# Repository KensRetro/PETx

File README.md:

# This project is currently partially complete, please read the following carefully and make an informed decision before you attempt to build it.

I like to provide schematics in Eagle (version 7) because that's what I have used for years at work and it's easy to upgrade the files to 
newer versions or Kicad etc.  It's just a comfort thing for me, but if you change to another format please be sure to carefully check 
that everything looks as it should - conversions don't always go cleanly.  

DISCLAIMER: All information is provided 'AS-IS", I have tried to be as accurate as possible but that doesn't mean there are no mistakes. 
Any errors or omissions etc. are your own responsibility.  

# Project Notes : C64 sized PET - PETx

The prototype is based on the the 9 inch screen version of the PET (board #320349) so no CRTC chip is needed.
I added the video circuit similar to the ones posted around the net
It was also decided to go with a more similar to original re-creation as it makes it easier to substitute parts etc. 
and compatibility remains quite good.

# Changes / Updates in this version (PROTOTYPE): 
1. Added connections for RESET (momentary switch)
2. Added NO_ROM line for diagnostics
3. Added peizo buzzer for standard PET sounds
4. Added Video output circuit - HORIZ/VERT/VIDEO signals no longer attached to USER PORT (I left connection points but will need a
   jumper to connect if needed. This was done in order to facilitate routing, these lines to the user port are normally used for a
   video output circuit, since it's already on-board, it's not likely needed)
5. Added GRAPHIC signal to USER PORT (similar to 12" screen versions)
6. Removed memory expansion connections, definitely won't fit on the board and no known expansion units will fit in the case anyway
7. Changed Video RAM to a single 6116 chip instead of 2 x 2114 (availability)
8. Change ROM set to a single chip, added necessary decoding logic so I/O chip memory is not replaced.
9. Added a jumper to allow multiple ROM sets built in (could be connected to a switch)
10. Changed RAM to a single chip of 32K, this also allowed removal of +12V and -5V supplies and associated components saving a lot of space.
11. Removed CASSETTE #2 as it is rarely used, connection points are still available but no driver for the tape motor was included.
    Connection would have to be wired off the board if needed.
12. Added a couple sets of connection points for +5V and GND for add-ons (normally CASSETTE #1/2 was used for this)
13. Added optional 2nd RAM chip mapped into 9000-FFFF range, jumper (or switch configurable) for only being active over 9000-AFFF or 9000-FFFF for soft ROM option
14. Added option for 2nd RAM (9000-FFFF) to be "READ ONLY" or "READ WRITE"
15. Terminated unused gates to minimize potential noise.
16. Changed ROM socket to allow use of SST39SF010A as well as 27256 (4 ROM sets, Flash ROM, externally programmable)
17. Changed Character ROM to allow more fonts and use of SST39SF010A as well as 27xxx series Eproms.
18. Added power switch & connector that should fit into the existing C64 bracket  (if used)
19. Added access to unused RAM in 8000 area (8400-8FFF)
    
# Potential upgrades not currently incorporated:
(Feel free to suggest others)
1. Add a writable latch that controls some of the dipswitch selectable features above
    
# More Notes:
This project is a PET 2001, 9 inch screen version (started with schematic 320349). This model was chosen for 2 reasons, 
first, a CRTC chip is not required and second, it outputs a near standard video signal with the included interface.
The Intent was to make it fit into a C64 / VIC-20 case.
In order to Achieve this a reduced footprint was needed, so the changes above were implemented.
The parallel and Cassette #1 ports were designed to line up in the same place as the C64/VIC20 version.
The video output appears where the RF output jack was on the C64. This area is in the cartridge slot on the VIC20
The IEEE port appears where the C64 cartridge port was and covers the left 2/3 of the VIC 20 cartridge area.
The placements mean that no/few modifications are needed to the case of the C64 or VIC 20 to fit the board in.
Unfortunately, the power switch and joystick area ends up wide open, with the power switch and power cord coming out in that area.
Perhaps a 3D printed cover could be fashioned as a replacement.
Many other possible upgrades were considered but due to a lack of space and complexity, were rejected (for the prototype run at least).
Perhaps other additions or changes could be incorporated in a future version.
This project depends on the Commodore original prints being correct, some minor corrections were caught, but they were used as a base to start.
The Chip ID's on the silkscreen are those from the original PET layout and start with Uxxx, Chips that start with ICxx are additions or changes 
that have been incorporated to slim the footprint or facilitate routing.
Various keyboard options were considered but again, for the prototype at least, were sticking with a standard C64/VIC20 keyboard and a patched 
version of the edit ROM (or some other available hardware solution)

# BEFORE YOU BUILD:
Some of the parts are near impossible to find, specifically 3446 chips, 74177 chips, and 74154 chips in a DIP package. 
I have a replacement sub-board for the 3446 chips in another repository that has been tested successfully.
You can use 74197 chips as a direct replacement for the 74177, but they are very rare as well.
You can use a newer version of the 74154 chip but it seems to only be available in a SMT version, therefore an adaptor board may need to be created.

# PROTOTYPE VERSION:
This version has been created and tested.  Some small errors were corrected with bodge wires and an added chip and and it seems to function well and passes the diagnostic 
cartridge tests consistantly.

# RELEASE VERSION:
This version HAS NOT been created or tested (I didn't really need another hanging around)
The errors have been corrected in the schematic and board files and Gerbers have been created.

Changes to this version (REV.1) also include the following:
1) Added solder jumpers to allow WD6502 to be used
2) Changed Power supply to 1 regulator
   
TO DO:
1. check/fix alignment of mounting holes to C64 case (Not checked or tested in VIC20 case at this time)

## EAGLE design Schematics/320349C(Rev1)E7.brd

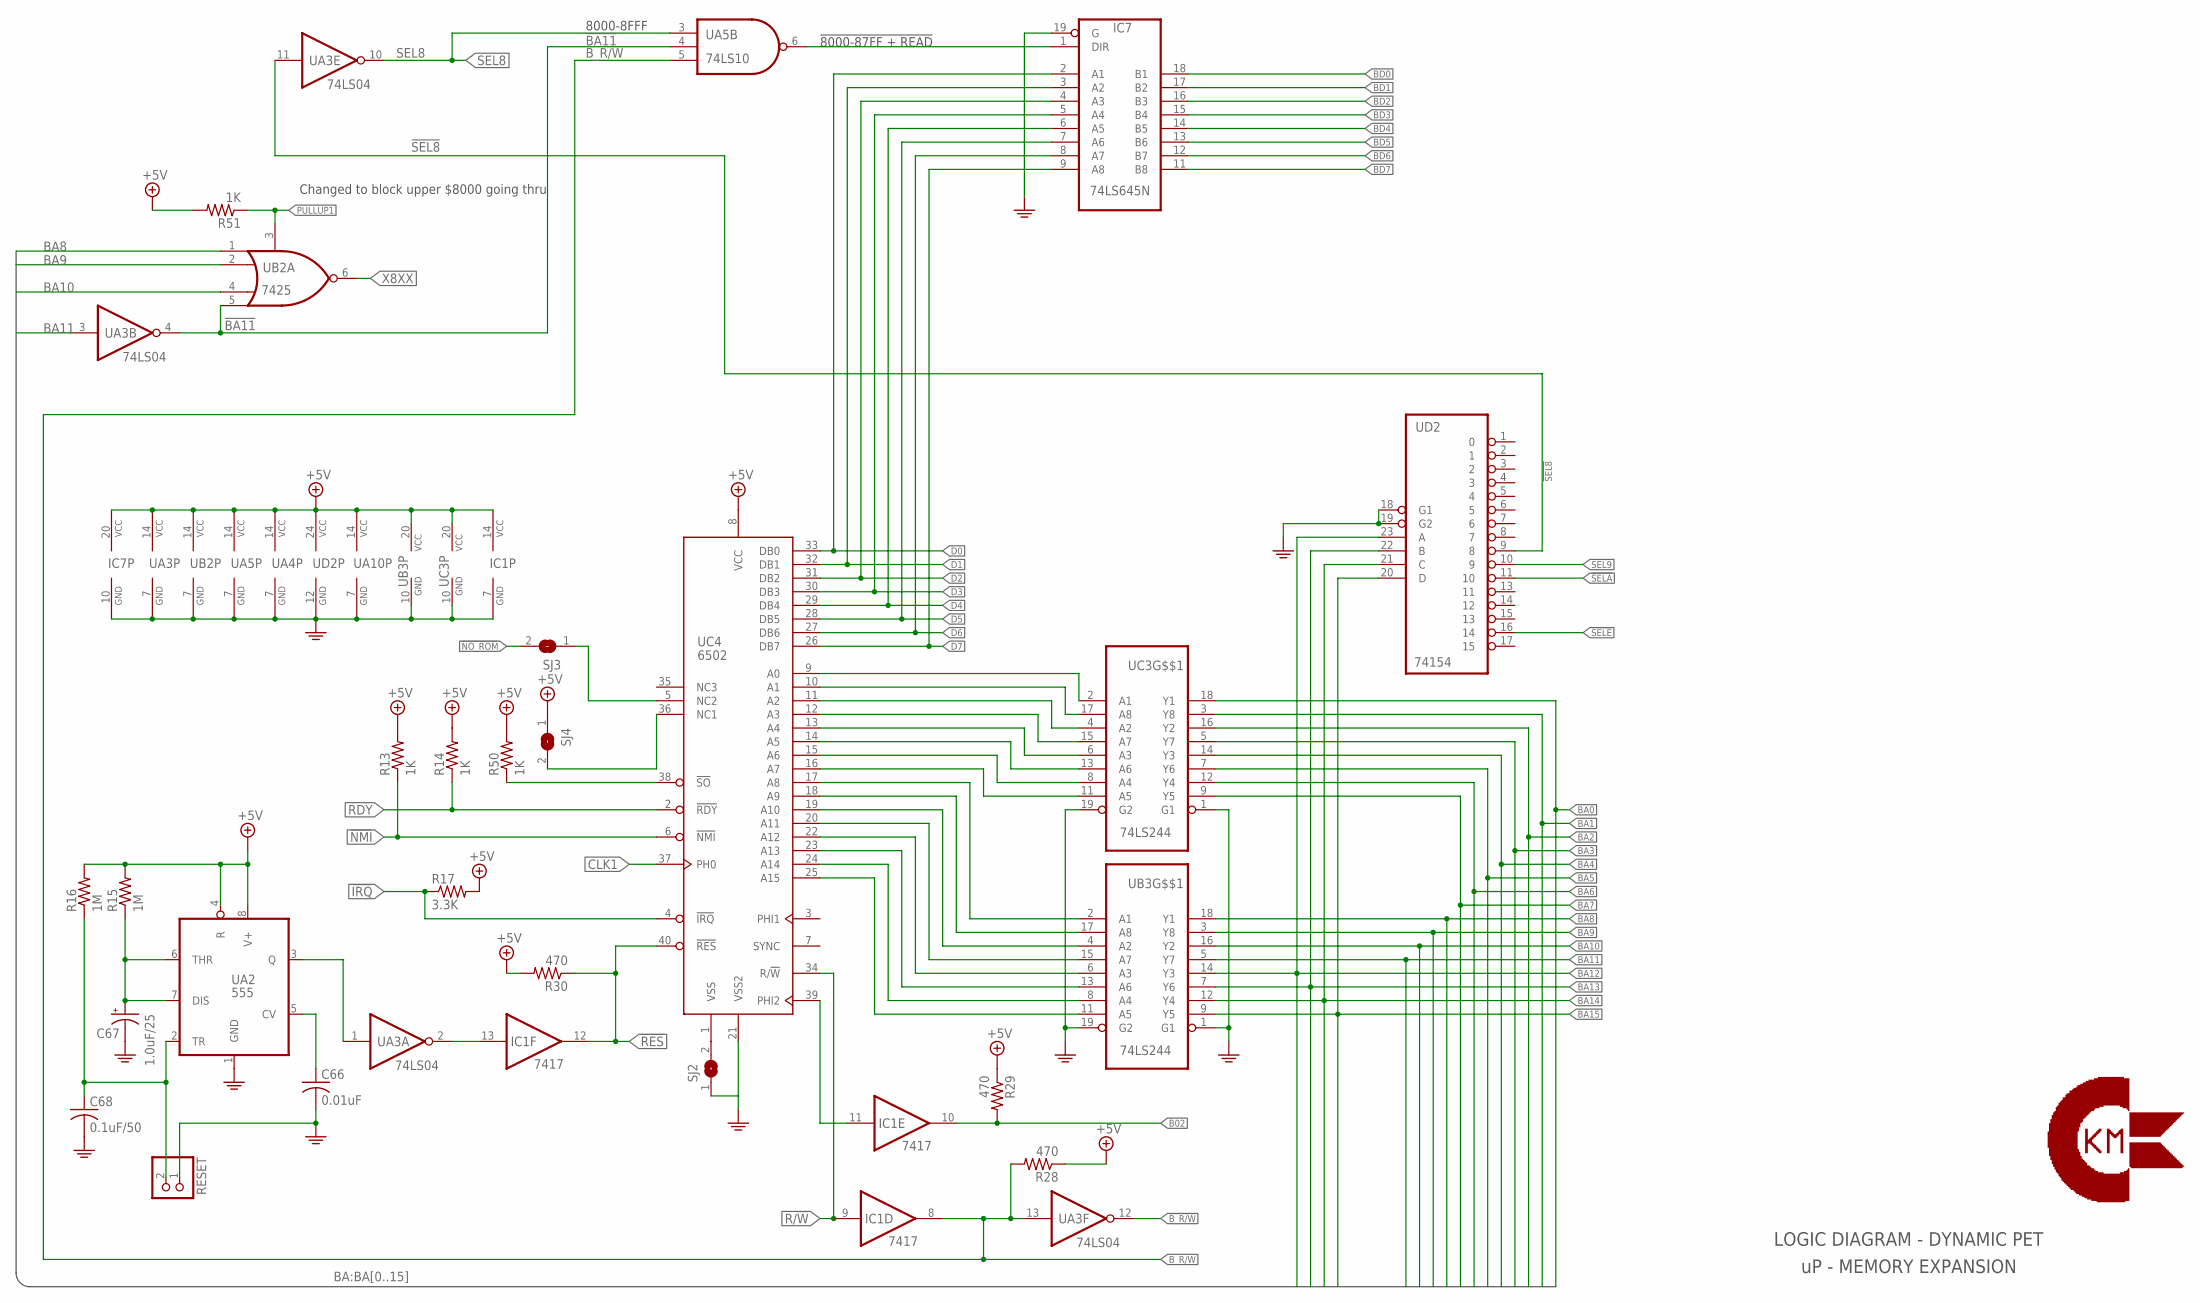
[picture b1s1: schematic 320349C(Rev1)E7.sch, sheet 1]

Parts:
C66: 0.01uF; C025-025X050
C67: 1.0uF/25; E2,5-5
C68: 0.1uF/50; C025-025X050
IC1: 7417; DIL14
IC7: 74LS645N; DIL20
R13, R14, R50, R51: 1K; 0207/10
R15, R16: 1M; 0207/10
R17: 3.3K; 0207/10
R28, R29, R30: 470; 0207/10
RESET: PINHD-1X2; 1X02
SJ2, SJ3, SJ4: SJ
UA2: 555; DIL08
UA3: 74LS04; DIL14
UA4: 74LS00; DIL14
UA5: 74LS10; DIL14
UA10: 7417; DIL14
UB2: 7425; DIL14
UB3: 74LS244; DIL20
UC3: 74LS244; DIL20
UC4: 6502; DIP40
UD2: 74154; DIL24-6

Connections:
!BA11: UA3.4 (O), UA5.4 (I1), UB2.5 (I3); also elsewhere on the board
!B_R/W: UA3.12 (O); also elsewhere on the board
!IRQ: R17.1, UC4.4 (!IRQ); also elsewhere on the board
!NMI: R13.1, UC4.6 (!NMI)
!NO_ROM: SJ3.2; also elsewhere on the board
!RES: IC1.12 (O), R30.1, UC4.40 (!RES); also elsewhere on the board
!SEL8: UA3.11 (I), UD2.9 (8); also elsewhere on the board
!SEL9: UD2.10 (9); also elsewhere on the board
!SELA: UD2.11 (10); also elsewhere on the board
!SELE: UD2.16 (14); also elsewhere on the board
+5V: IC1.14 (VCC), IC7.20 (VCC), R13.2, R14.2, R15.2, R16.2, R17.2, R28.1, R29.1, R30.2, R50.2, R51.2, SJ4.1, UA2.4 (R), UA2.8 (V+), UA3.14 (VCC), UA4.14 (VCC), UA5.14 (VCC), UA10.14 (VCC), UB2.14 (VCC), UB3.20 (VCC), UC3.20 (VCC), UC4.8 (VCC), UD2.24 (VCC); also elsewhere on the board
AB0: UC3.2 (A1), UC4.9 (A0)
AB1: UC3.17 (A8), UC4.10 (A1)
AB2: UC3.4 (A2), UC4.11 (A2)
AB3: UC3.15 (A7), UC4.12 (A3)
AB4: UC3.6 (A3), UC4.13 (A4)
AB5: UC3.13 (A6), UC4.14 (A5)
AB6: UC3.8 (A4), UC4.15 (A6)
AB7: UC3.11 (A5), UC4.16 (A7)
AB8: UB3.2 (A1), UC4.17 (A8)
AB9: UB3.17 (A8), UC4.18 (A9)
AB10: UB3.4 (A2), UC4.19 (A10)
AB11: UB3.15 (A7), UC4.20 (A11)
AB12: UB3.6 (A3), UC4.22 (A12)
AB13: UB3.13 (A6), UC4.23 (A13)
AB14: UB3.8 (A4), UC4.24 (A14)
AB15: UB3.11 (A5), UC4.25 (A15)
B02: IC1.10 (O), R29.2; also elsewhere on the board
BA0: UC3.18 (Y1); also elsewhere on the board
BA1: UC3.3 (Y8); also elsewhere on the board
BA2: UC3.16 (Y2); also elsewhere on the board
BA3: UC3.5 (Y7); also elsewhere on the board
BA4: UC3.14 (Y3); also elsewhere on the board
BA5: UC3.7 (Y6); also elsewhere on the board
BA6: UC3.12 (Y4); also elsewhere on the board
BA7: UC3.9 (Y5); also elsewhere on the board
BA8: UB2.1 (I0), UB3.18 (Y1); also elsewhere on the board
BA9: UB2.2 (I1), UB3.3 (Y8); also elsewhere on the board
BA10: UB2.4 (I2), UB3.16 (Y2); also elsewhere on the board
BA11: UA3.3 (I), UB3.5 (Y7); also elsewhere on the board
BA12: UB3.14 (Y3), UD2.23 (A); also elsewhere on the board
BA13: UB3.7 (Y6), UD2.22 (B); also elsewhere on the board
BA14: UB3.12 (Y4), UD2.21 (C); also elsewhere on the board
BA15: UB3.9 (Y5), UD2.20 (D); also elsewhere on the board
BD0: IC7.18 (B1); also elsewhere on the board
BD1: IC7.17 (B2); also elsewhere on the board
BD2: IC7.16 (B3); also elsewhere on the board
BD3: IC7.15 (B4); also elsewhere on the board
BD4: IC7.14 (B5); also elsewhere on the board
BD5: IC7.13 (B6); also elsewhere on the board
BD6: IC7.12 (B7); also elsewhere on the board
BD7: IC7.11 (B8); also elsewhere on the board
B_R/W: IC1.8 (O), R28.2, UA3.13 (I), UA5.5 (I2); also elsewhere on the board
CLK1: UC4.37 (PH0); also elsewhere on the board
CLK2: IC1.11 (I), UC4.39 (PHI2)
D0: IC7.2 (A1), UC4.33 (DB0); also elsewhere on the board
D1: IC7.3 (A2), UC4.32 (DB1); also elsewhere on the board
D2: IC7.4 (A3), UC4.31 (DB2); also elsewhere on the board
D3: IC7.5 (A4), UC4.30 (DB3); also elsewhere on the board
D4: IC7.6 (A5), UC4.29 (DB4); also elsewhere on the board
D5: IC7.7 (A6), UC4.28 (DB5); also elsewhere on the board
D6: IC7.8 (A7), UC4.27 (DB6); also elsewhere on the board
D7: IC7.9 (A8), UC4.26 (DB7); also elsewhere on the board
GND: C66.2, C67.-, C68.2, IC1.7 (GND), IC7.10 (GND), IC7.19 (G), RESET.1, SJ2.1, UA2.1 (GND), UA3.7 (GND), UA4.7 (GND), UA5.7 (GND), UA10.7 (GND), UB2.7 (GND), UB3.1 (G1), UB3.10 (GND), UB3.19 (G2), UC3.1 (G1), UC3.10 (GND), UC3.19 (G2), UC4.21 (VSS2), UD2.12 (GND), UD2.18 (G1), UD2.19 (G2); also elsewhere on the board
unnamed: IC7.1 (DIR), UA5.6 (O)
unnamed: R50.1, UC4.38 (!SO)
unnamed: C66.1, UA2.5 (CV)
unnamed: C67.+, R15.1, UA2.6 (THR), UA2.7 (DIS)
unnamed: C68.1, R16.1, RESET.2, UA2.2 (TR)
unnamed: IC1.13 (I), UA3.2 (O)
unnamed: UA2.3 (Q), UA3.1 (I)
unnamed: SJ3.1, UC4.5 (NC2)
unnamed: SJ4.2, UC4.36 (NC1)
unnamed: SJ2.2, UC4.1 (VSS)
PULLUP1: R51.1, UB2.3 (G); also elsewhere on the board
R/!W: IC1.9 (I), UC4.34 (R/!W); also elsewhere on the board
RDY: R14.1, UC4.2 (!RDY)
SEL8: UA3.10 (O), UA5.3 (I0); also elsewhere on the board
X8XX: UB2.6 (O); also elsewhere on the board

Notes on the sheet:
LOGIC DIAGRAM - DYNAMIC PET
uP - MEMORY EXPANSION
8000-8FFF
!8000-87FF + READ
Changed to block upper $8000 going thru

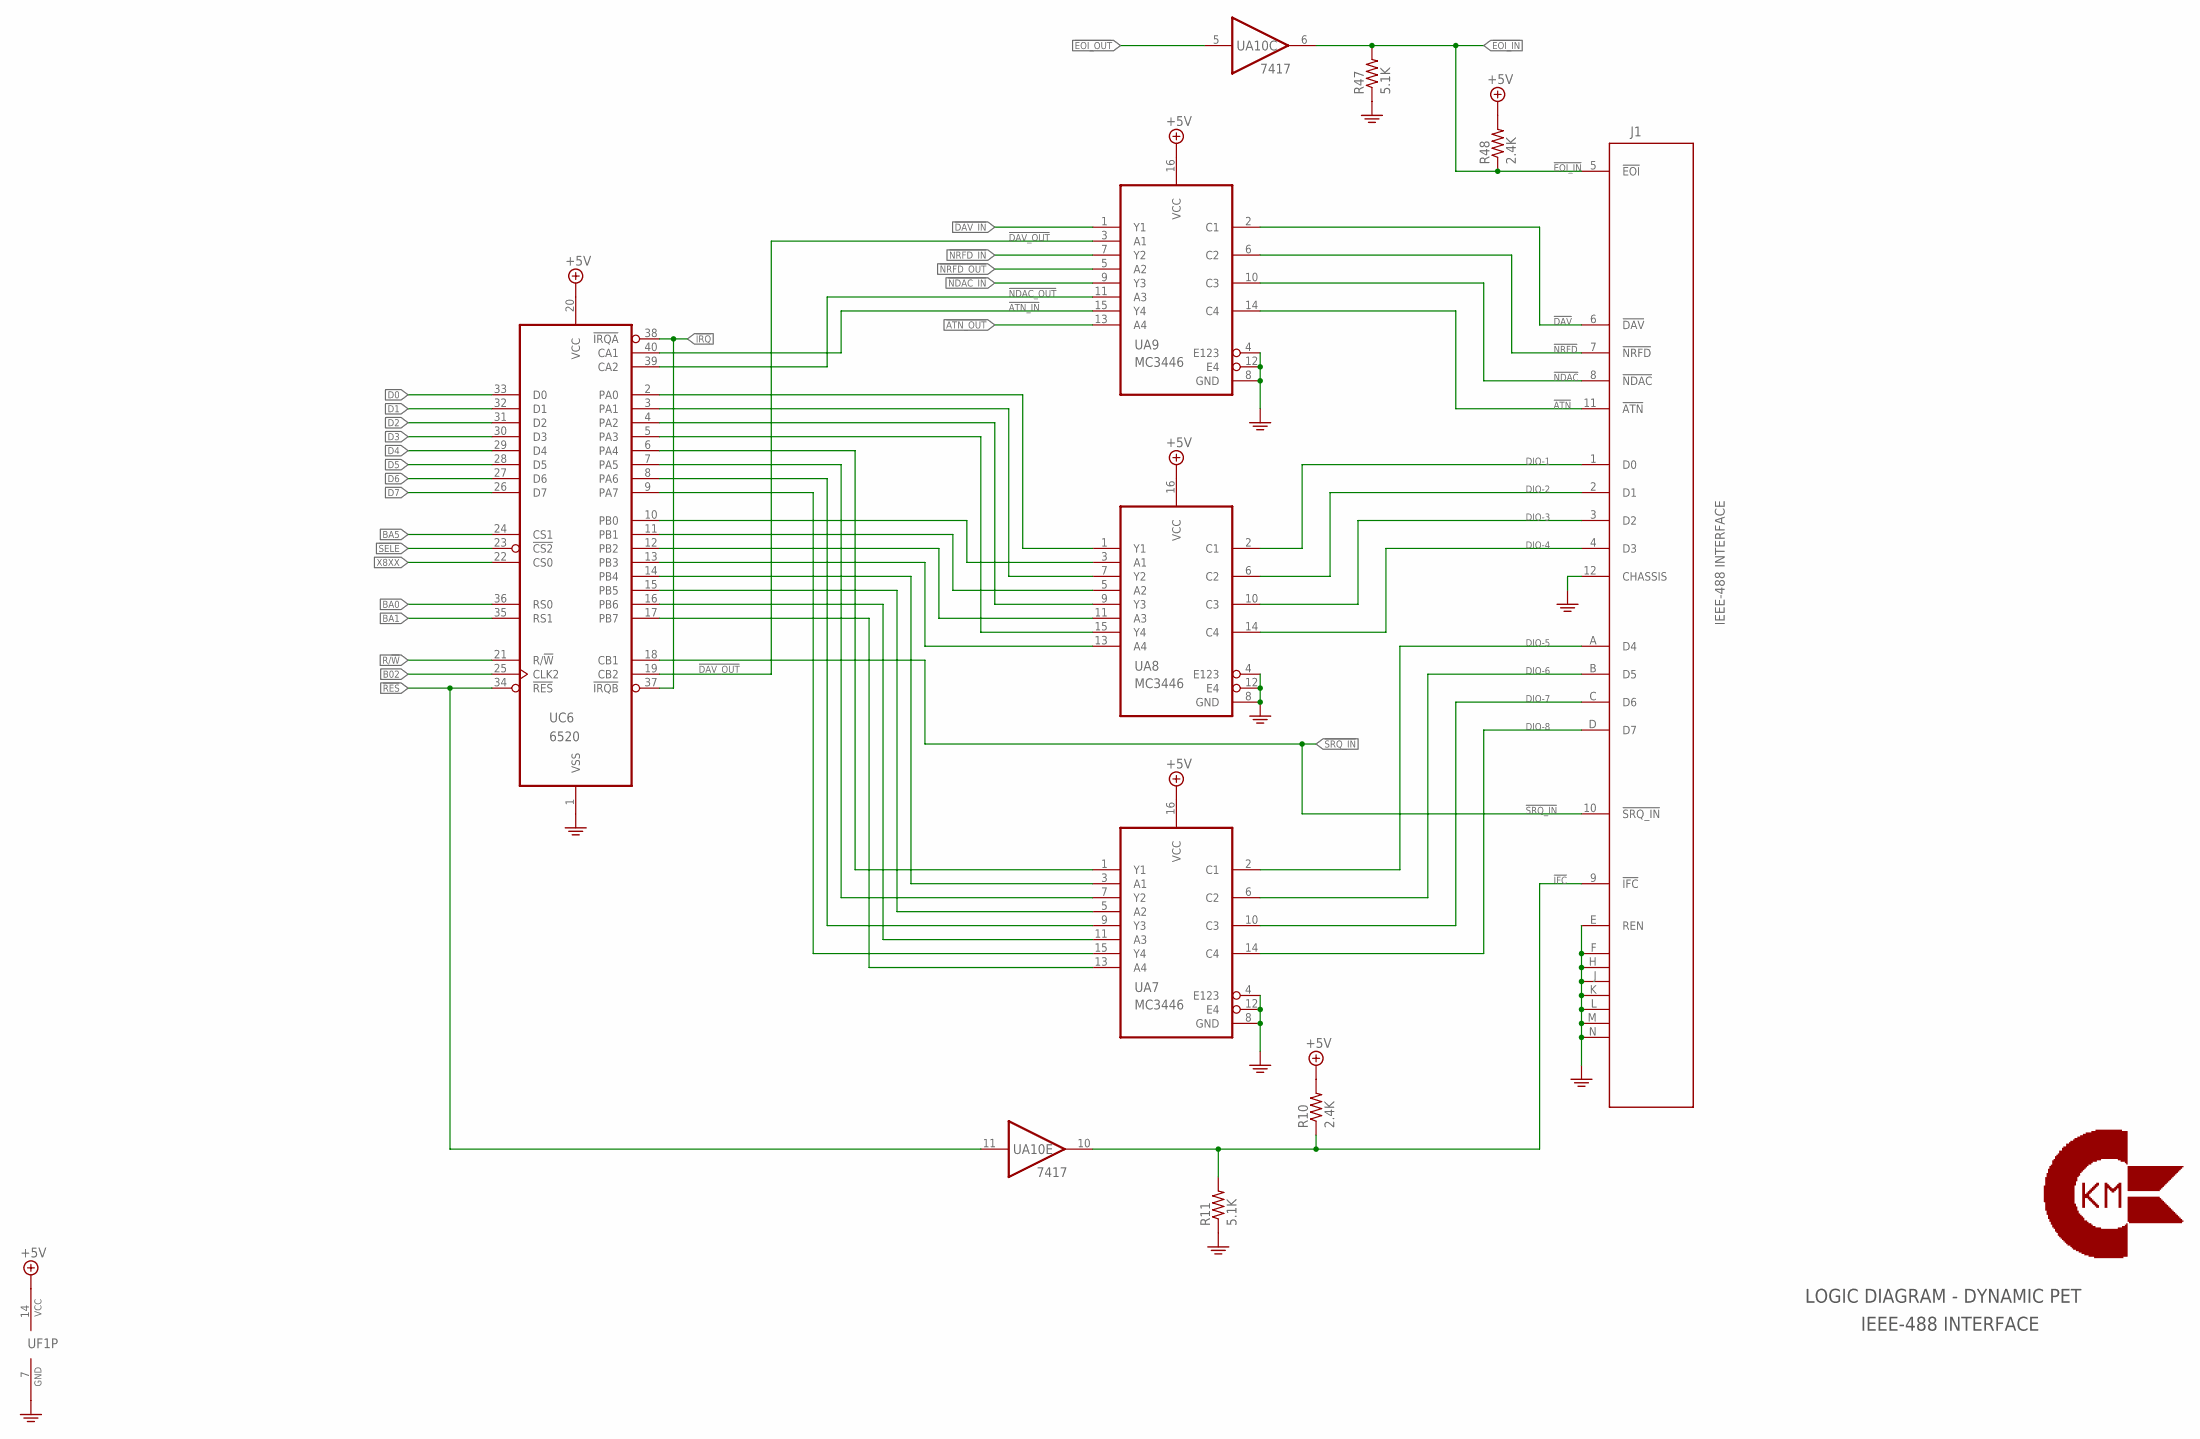
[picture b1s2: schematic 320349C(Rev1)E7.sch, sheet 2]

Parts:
J1: IEEE-488 INTERFACE; UPS24EDGE
R10, R48: 2.4K; 0207/10
R11, R47: 5.1K; 0207/10
U$32: CBM-XL
UA7, UA8, UA9: MC3446; DIL16
UA10: 7417; DIL14
UC6: 6520; DIL40
UF1: 74LS08; DIL14

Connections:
!ATN: J1.11 (!ATN), UA9.14 (C4)
!ATN_IN: UA9.15 (Y4), UC6.40 (CA1)
!ATN_OUT: UA9.13 (A4); also elsewhere on the board
!DAV: J1.6 (!DAV), UA9.2 (C1)
!DAV_IN: UA9.1 (Y1); also elsewhere on the board
!DAV_OUT: UA9.3 (A1), UC6.19 (CB2)
!EOI_IN: J1.5 (!EOI), R47.2, R48.1, UA10.6 (O); also elsewhere on the board
!EOI_OUT: UA10.5 (I); also elsewhere on the board
!IFC: J1.9 (!IFC), R10.1, R11.2, UA10.10 (O)
!IRQ: UC6.37 (!IRQB), UC6.38 (!IRQA); also elsewhere on the board
!NDAC: J1.8 (!NDAC), UA9.10 (C3)
!NDAC_IN: UA9.9 (Y3); also elsewhere on the board
!NDAC_OUT: UA9.11 (A3), UC6.39 (CA2)
!NRFD: J1.7 (!NRFD), UA9.6 (C2)
!NRFD_IN: UA9.7 (Y2); also elsewhere on the board
!NRFD_OUT: UA9.5 (A2); also elsewhere on the board
!RES: UA10.11 (I), UC6.34 (!RES); also elsewhere on the board
!SELE: UC6.23 (!CS2); also elsewhere on the board
!SRQ_IN: J1.10 (!SRQ_IN), UC6.18 (CB1); also elsewhere on the board
+5V: R10.2, R48.2, UA7.16 (VCC), UA8.16 (VCC), UA9.16 (VCC), UC6.20 (VCC), UF1.14 (VCC); also elsewhere on the board
B02: UC6.25 (CLK2); also elsewhere on the board
BA0: UC6.36 (RS0); also elsewhere on the board
BA1: UC6.35 (RS1); also elsewhere on the board
BA5: UC6.24 (CS1); also elsewhere on the board
D0: UC6.33 (D0); also elsewhere on the board
D1: UC6.32 (D1); also elsewhere on the board
D2: UC6.31 (D2); also elsewhere on the board
D3: UC6.30 (D3); also elsewhere on the board
D4: UC6.29 (D4); also elsewhere on the board
D5: UC6.28 (D5); also elsewhere on the board
D6: UC6.27 (D6); also elsewhere on the board
D7: UC6.26 (D7); also elsewhere on the board
DI-1: UA8.1 (Y1), UC6.2 (PA0)
DI-2: UA8.7 (Y2), UC6.3 (PA1)
DI-3: UA8.9 (Y3), UC6.4 (PA2)
DI-4: UA8.15 (Y4), UC6.5 (PA3)
DI-5: UA7.1 (Y1), UC6.6 (PA4)
DI-6: UA7.7 (Y2), UC6.7 (PA5)
DI-7: UA7.9 (Y3), UC6.8 (PA6)
DI-8: UA7.15 (Y4), UC6.9 (PA7)
DIO-1: J1.1 (D0), UA8.2 (C1)
DIO-2: J1.2 (D1), UA8.6 (C2)
DIO-3: J1.3 (D2), UA8.10 (C3)
DIO-4: J1.4 (D3), UA8.14 (C4)
DIO-5: J1.A (D4), UA7.2 (C1)
DIO-6: J1.B (D5), UA7.6 (C2)
DIO-7: J1.C (D6), UA7.10 (C3)
DIO-8: J1.D (D7), UA7.14 (C4)
DO-1: UA8.3 (A1), UC6.10 (PB0)
DO-2: UA8.5 (A2), UC6.11 (PB1)
DO-3: UA8.11 (A3), UC6.12 (PB2)
DO-4: UA8.13 (A4), UC6.13 (PB3)
DO-5: UA7.3 (A1), UC6.14 (PB4)
DO-6: UA7.5 (A2), UC6.15 (PB5)
DO-7: UA7.11 (A3), UC6.16 (PB6)
DO-8: UA7.13 (A4), UC6.17 (PB7)
GND: J1.12 (CHASSIS), J1.E (REN), J1.F (18), J1.H (19), J1.J (20), J1.K (21), J1.L (22), J1.M (23), J1.N (24), R11.1, R47.1, UA7.4 (E123), UA7.8 (GND), UA7.12 (E4), UA8.4 (E123), UA8.8 (GND), UA8.12 (E4), UA9.4 (E123), UA9.8 (GND), UA9.12 (E4), UC6.1 (VSS), UF1.7 (GND); also elsewhere on the board
R/!W: UC6.21 (R/!W); also elsewhere on the board
X8XX: UC6.22 (CS0); also elsewhere on the board

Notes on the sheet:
LOGIC DIAGRAM - DYNAMIC PET
IEEE-488 INTERFACE

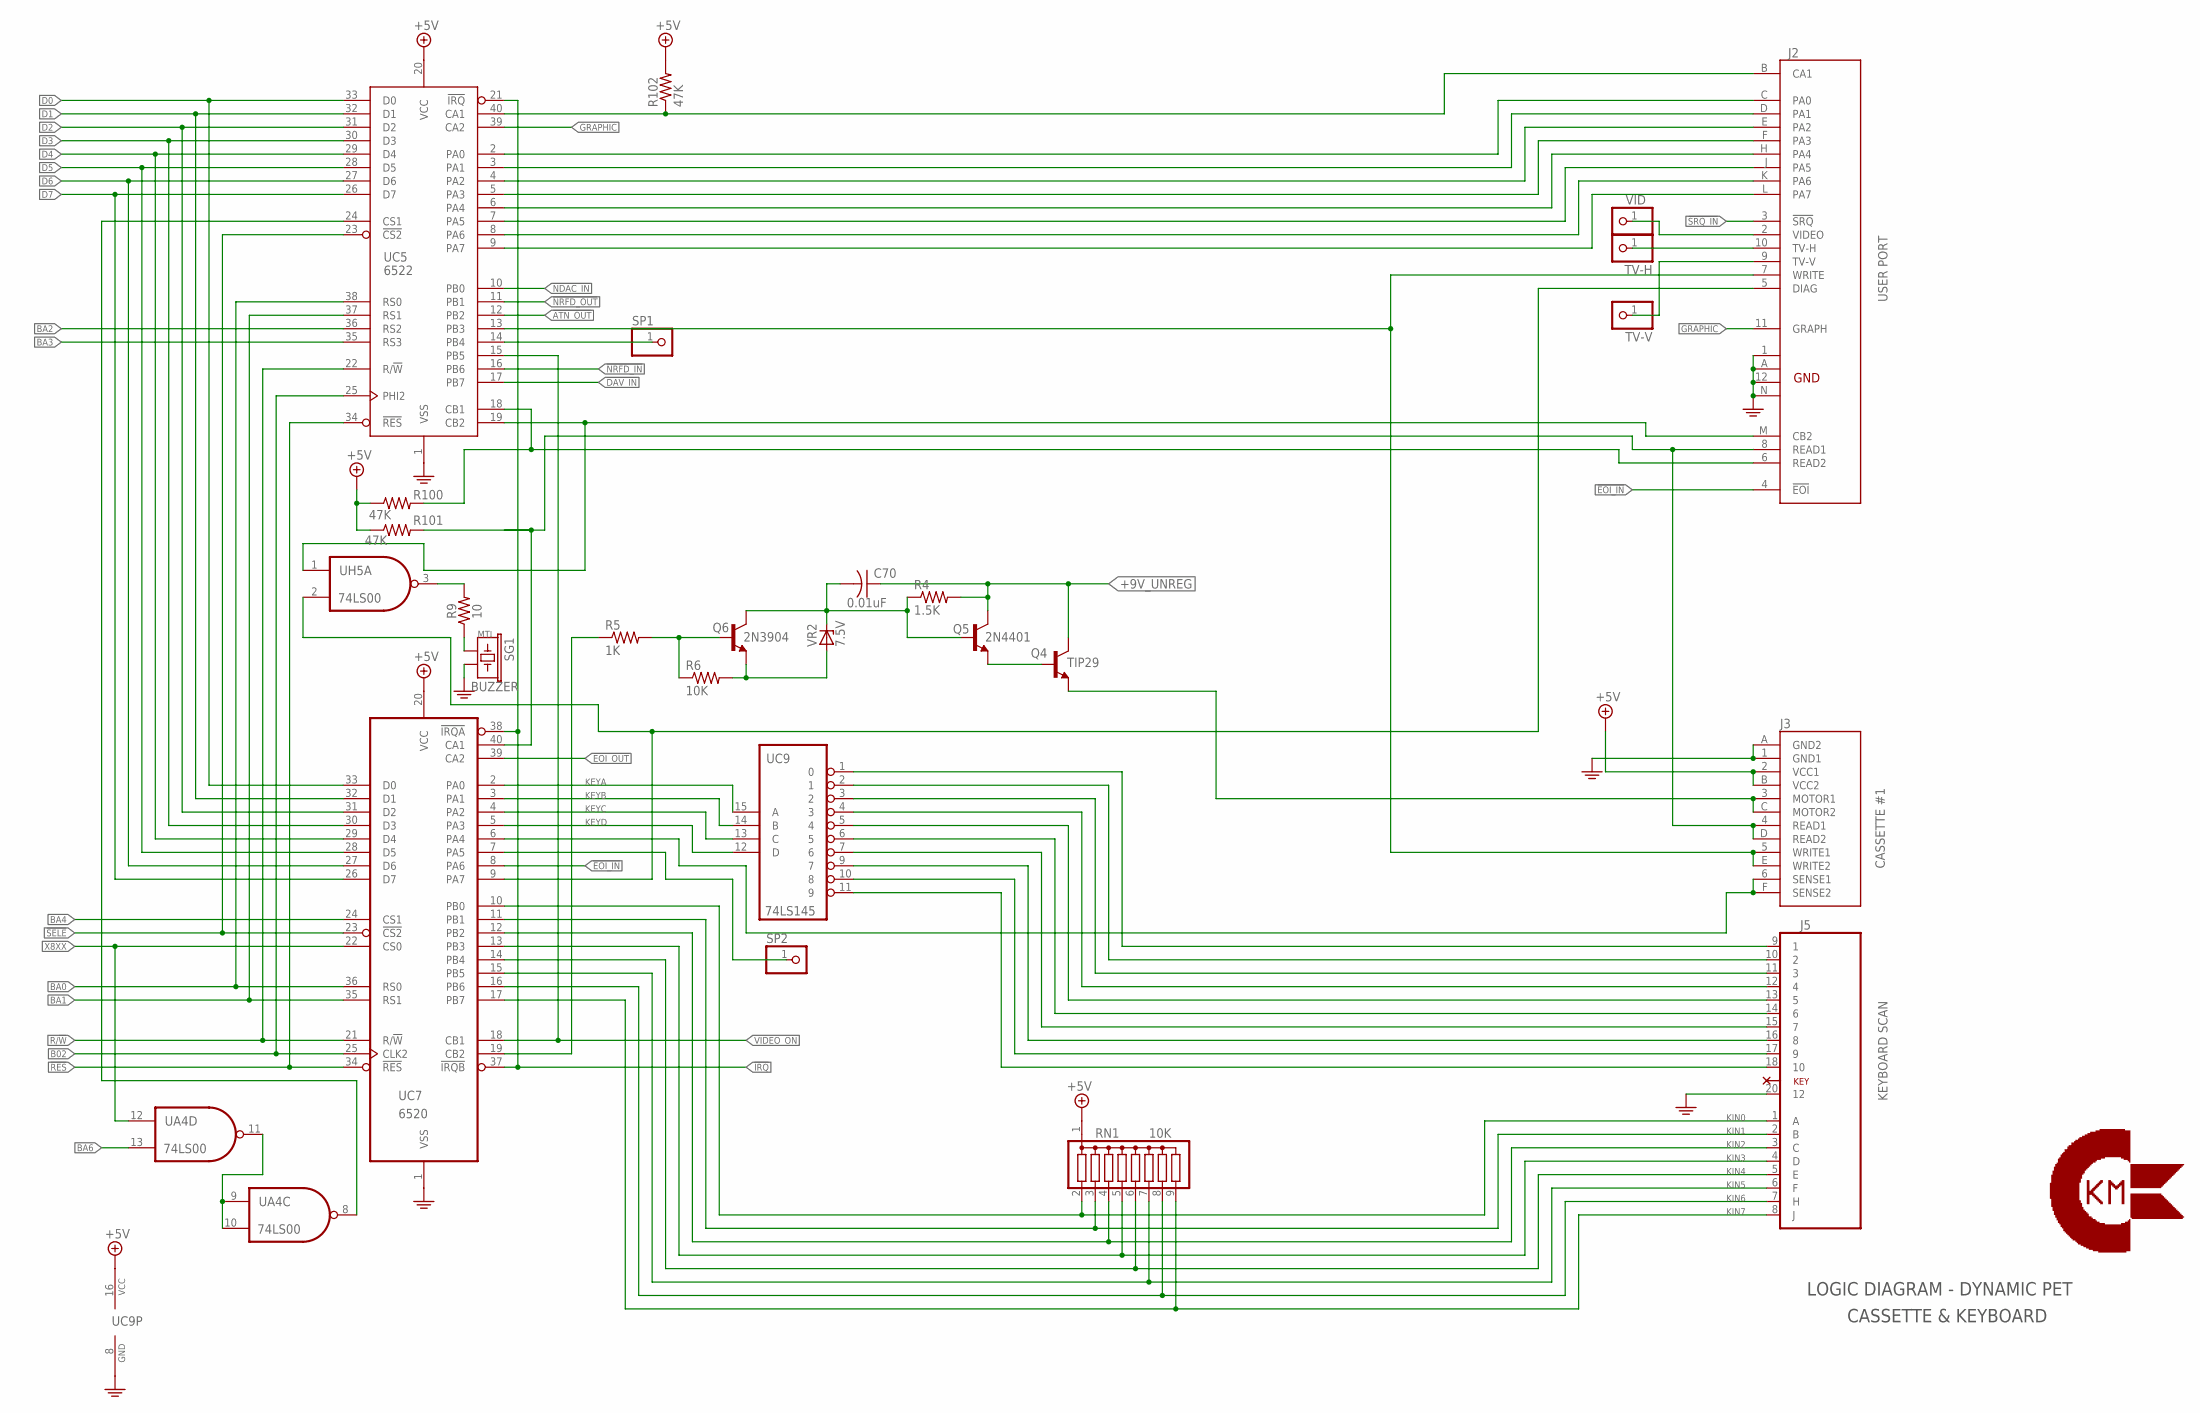
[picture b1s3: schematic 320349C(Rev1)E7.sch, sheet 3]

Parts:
C70: 0.01uF; C025-025X050
J2: USER PORT; UPS24EDGE
J3: CASSETTE #1; CASSETTE
J5: KEYBOARD SCAN; PET_KEYBOARD
Q4: TIP29; TO220
Q5: 2N4401; TO92
Q6: 2N3904; TO92
R4: 1.5K; 0207/10
R5: 1K; 0207/10
R6: 10K; 0207/10
R9: 10; 0207/10
R100, R101, R102: 47K; 0207/10
RN1: 10K; SIL9
SG1: BUZZER; BUZZER-12MM
SP1, SP2: PINHD-1X1; 1X01
TV-H: PINHD-1X1; 1X01
TV-V: PINHD-1X1; 1X01
UA4: 74LS00; DIL14
UC5: 6522; DIP40
UC7: 6520; DIL40
UC9: 74LS145; DIL16
UH5: 74LS00; DIL14
VID: PINHD-1X1; 1X01
VR2: 7.5V; DO41Z10

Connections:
!ATN_OUT: UC5.12 (PB2); also elsewhere on the board
!DAV_IN: UC5.17 (PB7); also elsewhere on the board
!EOI_IN: J2.4 (!EOI), UC7.8 (PA6); also elsewhere on the board
!EOI_OUT: UC7.39 (CA2); also elsewhere on the board
!IRQ: UC5.21 (!IRQ), UC7.37 (!IRQB), UC7.38 (!IRQA); also elsewhere on the board
!NDAC_IN: UC5.10 (PB0); also elsewhere on the board
!NRFD_IN: UC5.16 (PB6); also elsewhere on the board
!NRFD_OUT: UC5.11 (PB1); also elsewhere on the board
!RES: UC5.34 (!RES), UC7.34 (!RES); also elsewhere on the board
!SELE: UC5.23 (!CS2), UC7.23 (!CS2); also elsewhere on the board
!SRQ_IN: J2.3 (!SRQ); also elsewhere on the board
#1_CASS_MOTOR: J3.3 (MOTOR1), J3.C (MOTOR2), Q4.3 (E)
#1_CASS_READ: J2.8 (READ1), J3.4 (READ1), J3.D (READ2), R101.2, UC7.40 (CA1)
#1_CASS_SWITCH: J3.6 (SENSE1), J3.F (SENSE2), UC7.6 (PA4)
#2_CASS_READ: J2.6 (READ2), R100.2, UC5.18 (CB1)
#2_CASS_SWITCH: SP2.1, UC7.7 (PA5)
+5V: J3.2 (VCC1), J3.B (VCC2), R100.1, R101.1, R102.2, RN1.1, UC5.20 (VCC), UC7.20 (VCC), UC9.16 (VCC); also elsewhere on the board
+9V_UNREG: C70.1, Q4.2 (C), Q5.1 (C), R4.2; also elsewhere on the board
B02: UC5.25 (PHI2), UC7.25 (CLK2); also elsewhere on the board
BA0: UC5.38 (RS0), UC7.36 (RS0); also elsewhere on the board
BA1: UC5.37 (RS1), UC7.35 (RS1); also elsewhere on the board
BA2: UC5.36 (RS2); also elsewhere on the board
BA3: UC5.35 (RS3); also elsewhere on the board
BA4: UC7.24 (CS1); also elsewhere on the board
BA6: UA4.13 (I1); also elsewhere on the board
CA1: J2.B (CA1), R102.1, UC5.40 (CA1)
CASS_WRITE: J2.7 (WRITE), J3.5 (WRITE1), J3.E (WRITE2), UC5.13 (PB3)
CB2: J2.M (CB2), UC5.19 (CB2), UH5.1 (I0)
CS1: UA4.8 (O), UC5.24 (CS1)
D0: UC5.33 (D0), UC7.33 (D0); also elsewhere on the board
D1: UC5.32 (D1), UC7.32 (D1); also elsewhere on the board
D2: UC5.31 (D2), UC7.31 (D2); also elsewhere on the board
D3: UC5.30 (D3), UC7.30 (D3); also elsewhere on the board
D4: UC5.29 (D4), UC7.29 (D4); also elsewhere on the board
D5: UC5.28 (D5), UC7.28 (D5); also elsewhere on the board
D6: UC5.27 (D6), UC7.27 (D6); also elsewhere on the board
D7: UC5.26 (D7), UC7.26 (D7); also elsewhere on the board
DIAG: J2.5 (DIAG), UC7.9 (PA7), UH5.2 (I1)
GND: J2.1 (GND1), J2.12 (GND3), J2.A (GND2), J2.N (GND4), J3.1 (GND1), J3.A (GND2), J5.20 (12), SG1.- (2), UC5.1 (VSS), UC7.1 (VSS), UC9.8 (GND); also elsewhere on the board
GRAPHIC: J2.11 (GRAPH), UC5.39 (CA2); also elsewhere on the board
KEYA: UC7.2 (PA0), UC9.15 (A)
KEYB: UC7.3 (PA1), UC9.14 (B)
KEYC: UC7.4 (PA2), UC9.13 (C)
KEYD: UC7.5 (PA3), UC9.12 (D)
KIN0: J5.1 (A), RN1.2, UC7.10 (PB0)
KIN1: J5.2 (B), RN1.3, UC7.11 (PB1)
KIN2: J5.3 (C), RN1.4, UC7.12 (PB2)
KIN3: J5.4 (D), RN1.5, UC7.13 (PB3)
KIN4: J5.5 (E), RN1.6, UC7.14 (PB4)
KIN5: J5.6 (F), RN1.7, UC7.15 (PB5)
KIN6: J5.7 (H), RN1.8, UC7.16 (PB6)
KIN7: J5.8 (J), RN1.9, UC7.17 (PB7)
unnamed: R9.2, UH5.3 (O)
unnamed: R9.1, SG1.+ (1)
unnamed: J2.2 (VIDEO), VID.1
unnamed: J2.10 (TV-H), TV-H.1
unnamed: J2.9 (TV-V), TV-V.1
unnamed: UA4.9 (I0), UA4.10 (I1), UA4.11 (O)
unnamed: SP1.1, UC5.14 (PB4)
unnamed: Q6.2 (B), R5.2, R6.1
unnamed: Q6.3 (E), R6.2, VR2.A
unnamed: C70.2, Q5.2 (B), Q6.1 (C), R4.1, VR2.C
unnamed: Q4.1 (B), Q5.3 (E)
unnamed: R5.1, UC7.19 (CB2)
unnamed: J5.18 (10), UC9.11 (9)
unnamed: J5.17 (9), UC9.10 (8)
unnamed: J5.16 (8), UC9.9 (7)
unnamed: J5.15 (7), UC9.7 (6)
unnamed: J5.14 (6), UC9.6 (5)
unnamed: J5.13 (5), UC9.5 (4)
unnamed: J5.12 (4), UC9.4 (3)
unnamed: J5.11 (3), UC9.3 (2)
unnamed: J5.10 (2), UC9.2 (1)
unnamed: J5.9 (1), UC9.1 (0)
PA0: J2.C (PA0), UC5.2 (PA0)
PA1: J2.D (PA1), UC5.3 (PA1)
PA2: J2.E (PA2), UC5.4 (PA2)
PA3: J2.F (PA3), UC5.5 (PA3)
PA4: J2.H (PA4), UC5.6 (PA4)
PA5: J2.J (PA5), UC5.7 (PA5)
PA6: J2.K (PA6), UC5.8 (PA6)
PA7: J2.L (PA7), UC5.9 (PA7)
R/!W: UC5.22 (R/!W), UC7.21 (R/!W); also elsewhere on the board
VIDEO_ON: UC5.15 (PB5), UC7.18 (CB1); also elsewhere on the board
X8XX: UA4.12 (I0), UC7.22 (CS0); also elsewhere on the board

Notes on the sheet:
LOGIC DIAGRAM - DYNAMIC PET
CASSETTE & KEYBOARD
MTI

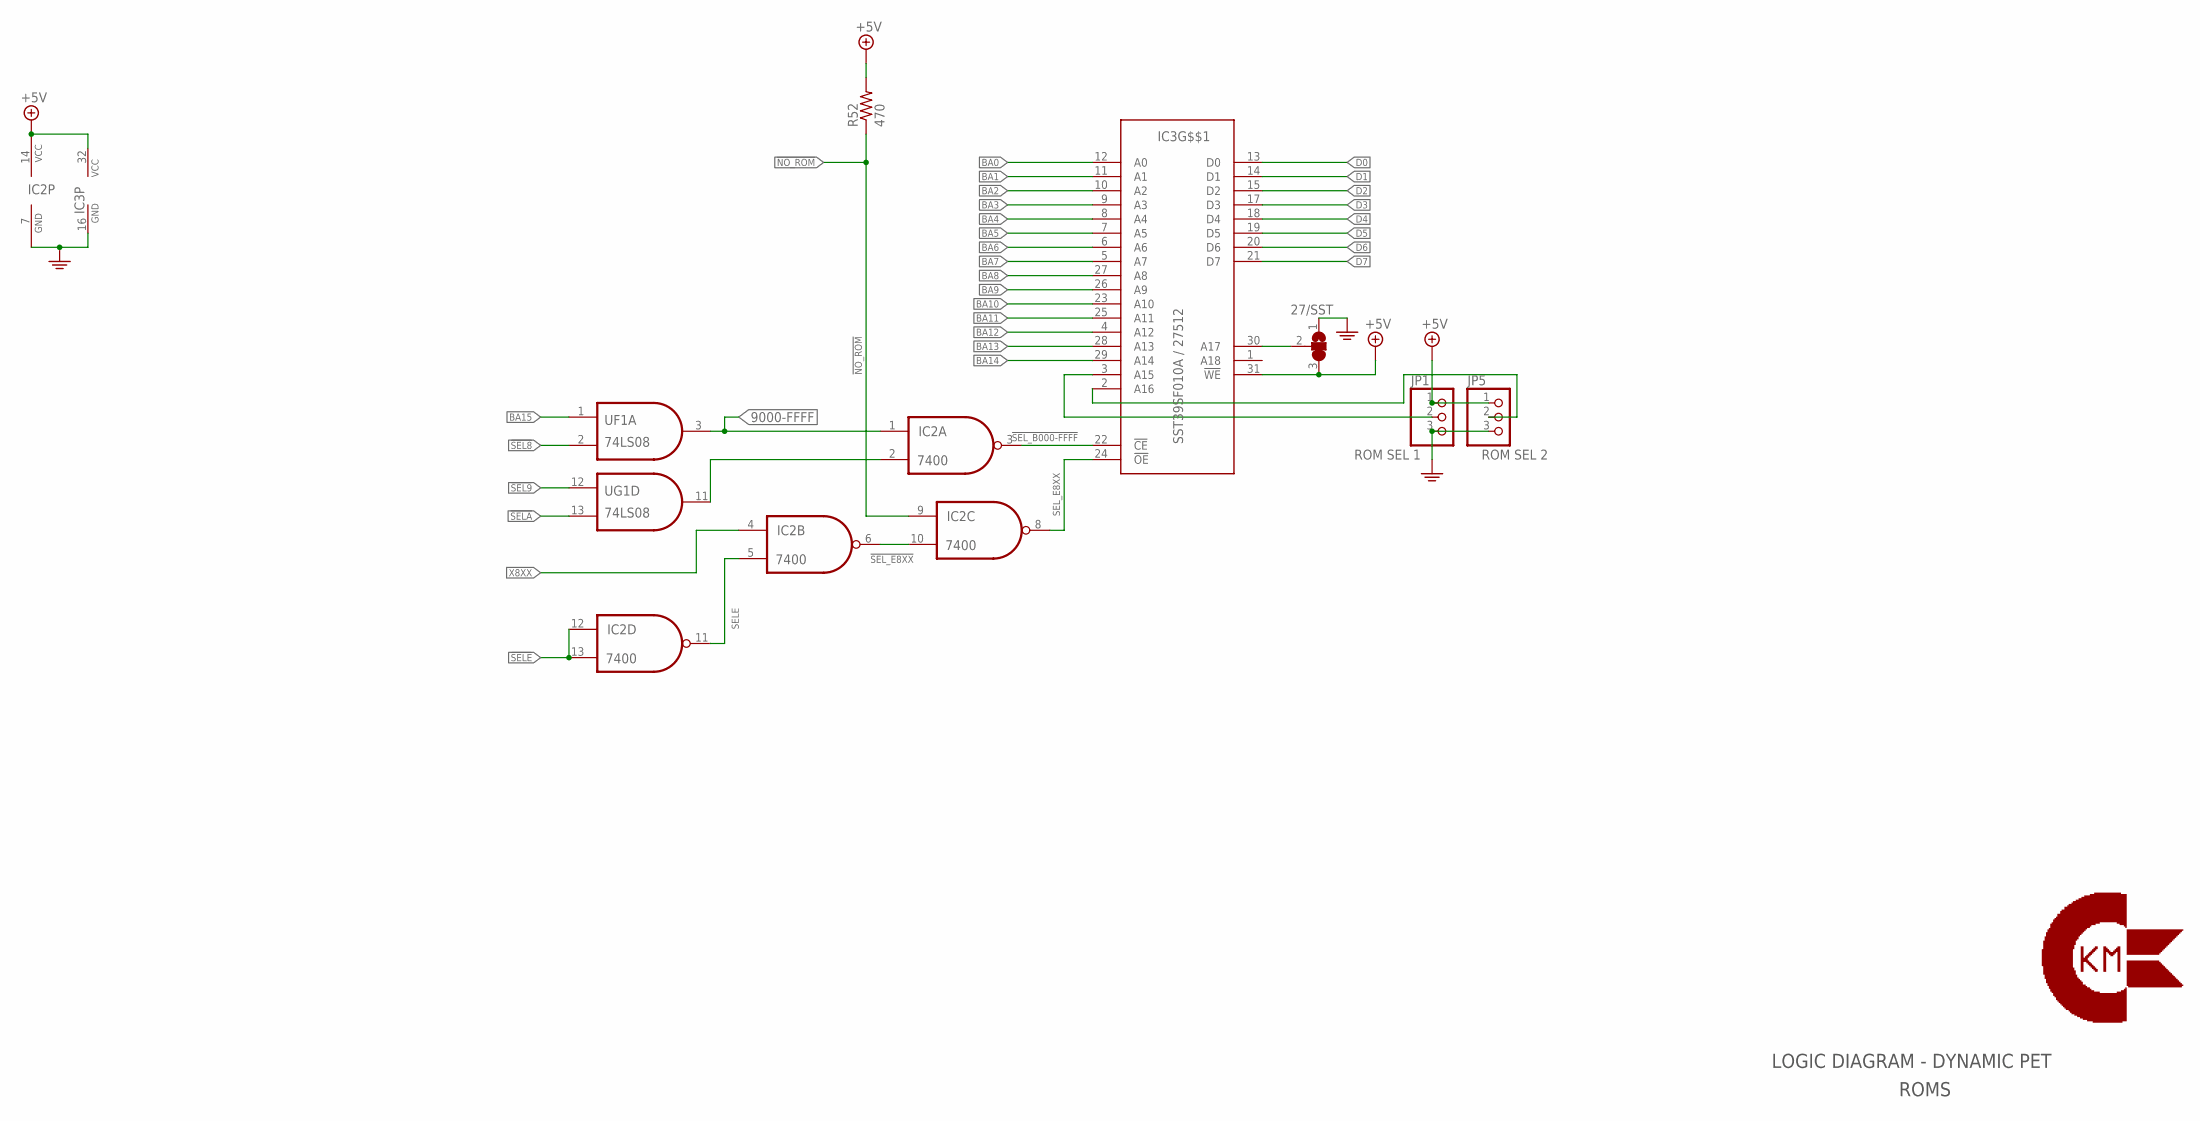
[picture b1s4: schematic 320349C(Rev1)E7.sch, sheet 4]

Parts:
27/SST: 27/SST; SJ_2
IC2: 7400; DIL14
IC3: SST39SF010A / 27512; SST39SF010A
JP1: ROM SEL 1; 1X03
JP5: ROM SEL 2; 1X03
R52: 470; 0207/10
UF1: 74LS08; DIL14
UG1: 74LS08; DIL14

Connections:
9000-FFFF: IC2.1 (I0), UF1.3 (O); also elsewhere on the board
!NO_ROM: IC2.9 (I0), R52.1; also elsewhere on the board
!SEL8: UF1.2 (I1); also elsewhere on the board
!SEL9: UG1.12 (I0); also elsewhere on the board
!SELA: UG1.13 (I1); also elsewhere on the board
!SELE: IC2.12 (I0), IC2.13 (I1); also elsewhere on the board
!SEL_B000-FFFF: IC2.3 (O), IC3.22 (!CE)
!SEL_E8XX: IC2.6 (O), IC2.10 (I1); also elsewhere on the board
+5V: 27/SST.3, IC2.14 (VCC), IC3.31 (!WE), IC3.32 (VCC), JP1.1, JP5.1, R52.2; also elsewhere on the board
BA0: IC3.12 (A0); also elsewhere on the board
BA1: IC3.11 (A1); also elsewhere on the board
BA2: IC3.10 (A2); also elsewhere on the board
BA3: IC3.9 (A3); also elsewhere on the board
BA4: IC3.8 (A4); also elsewhere on the board
BA5: IC3.7 (A5); also elsewhere on the board
BA6: IC3.6 (A6); also elsewhere on the board
BA7: IC3.5 (A7); also elsewhere on the board
BA8: IC3.27 (A8); also elsewhere on the board
BA9: IC3.26 (A9); also elsewhere on the board
BA10: IC3.23 (A10); also elsewhere on the board
BA11: IC3.25 (A11); also elsewhere on the board
BA12: IC3.4 (A12); also elsewhere on the board
BA13: IC3.28 (A13); also elsewhere on the board
BA14: IC3.29 (A14); also elsewhere on the board
BA15: UF1.1 (I0); also elsewhere on the board
D0: IC3.13 (D0); also elsewhere on the board
D1: IC3.14 (D1); also elsewhere on the board
D2: IC3.15 (D2); also elsewhere on the board
D3: IC3.17 (D3); also elsewhere on the board
D4: IC3.18 (D4); also elsewhere on the board
D5: IC3.19 (D5); also elsewhere on the board
D6: IC3.20 (D6); also elsewhere on the board
D7: IC3.21 (D7); also elsewhere on the board
GND: 27/SST.1, IC2.7 (GND), IC3.16 (GND), JP1.3, JP5.3; also elsewhere on the board
unnamed: IC2.2 (I1), UG1.11 (O)
unnamed: IC3.3 (A15), JP1.2
unnamed: IC3.2 (A16), JP5.2
unnamed: 27/SST.2, IC3.30 (A17)
SELE: IC2.5 (I1), IC2.11 (O)
SEL_E8XX: IC2.8 (O), IC3.24 (!OE)
X8XX: IC2.4 (I0); also elsewhere on the board

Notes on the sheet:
LOGIC DIAGRAM - DYNAMIC PET
ROMS
